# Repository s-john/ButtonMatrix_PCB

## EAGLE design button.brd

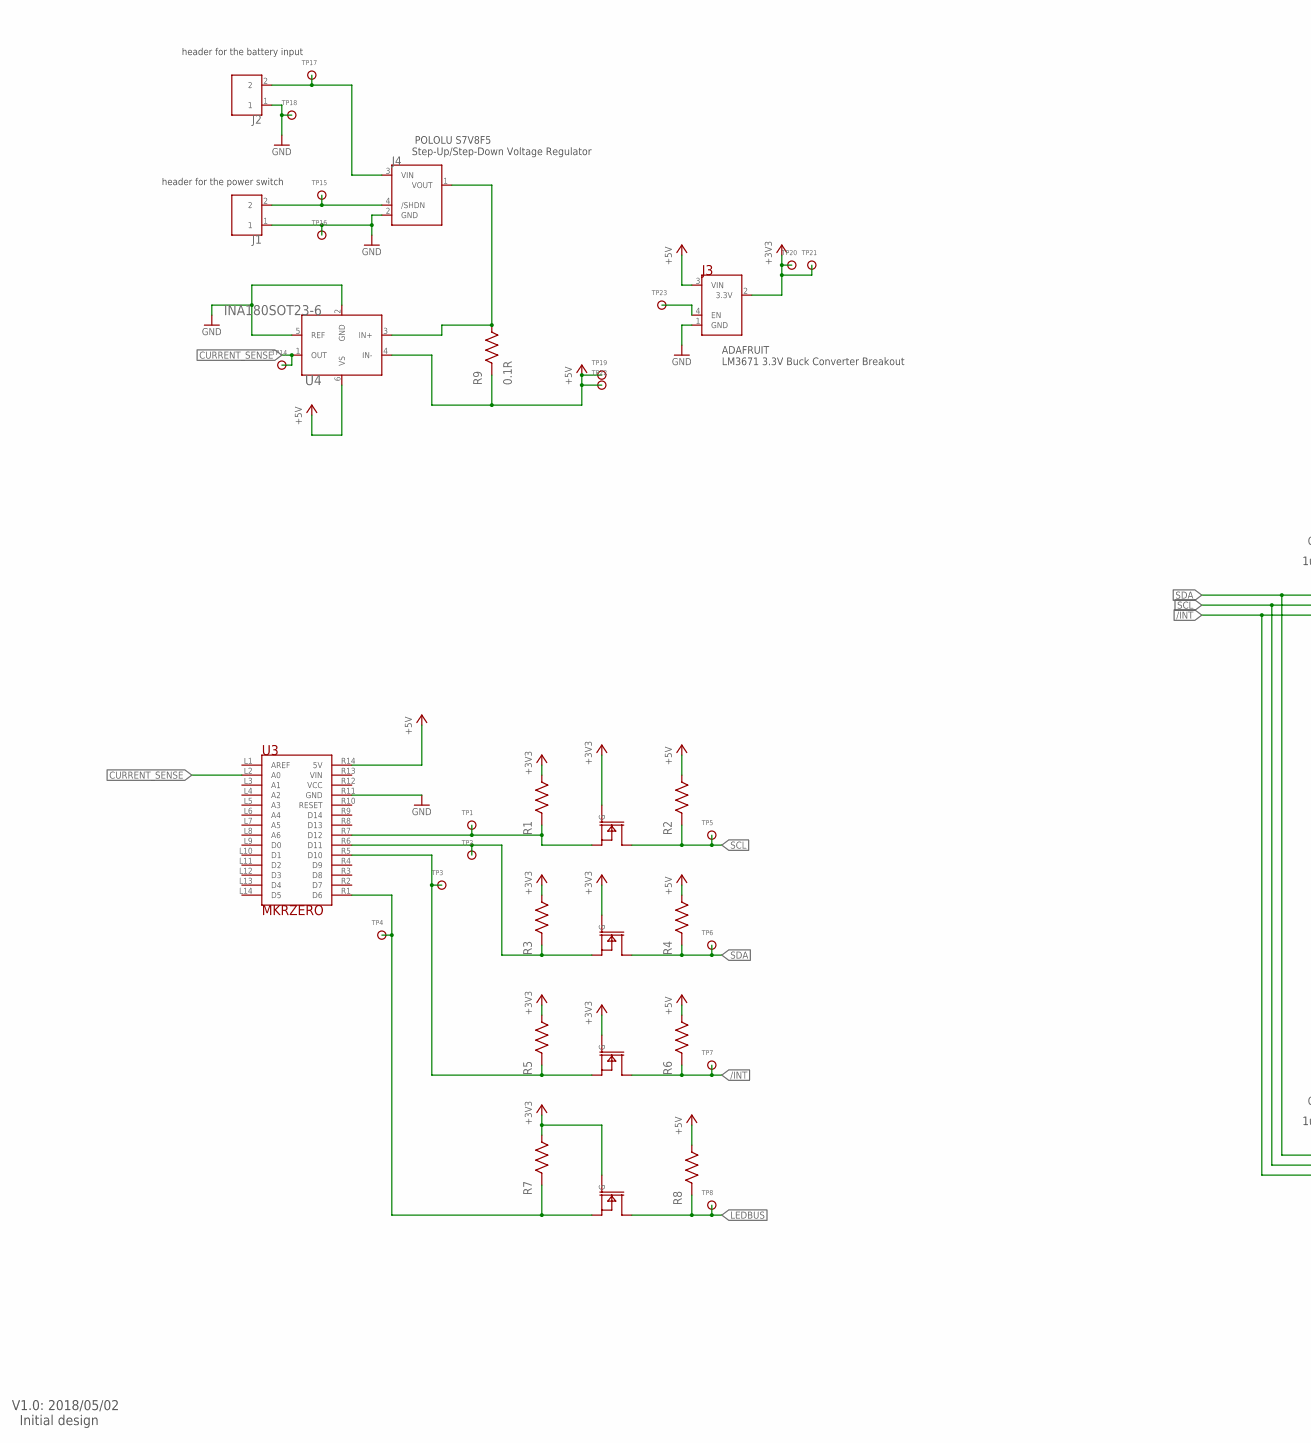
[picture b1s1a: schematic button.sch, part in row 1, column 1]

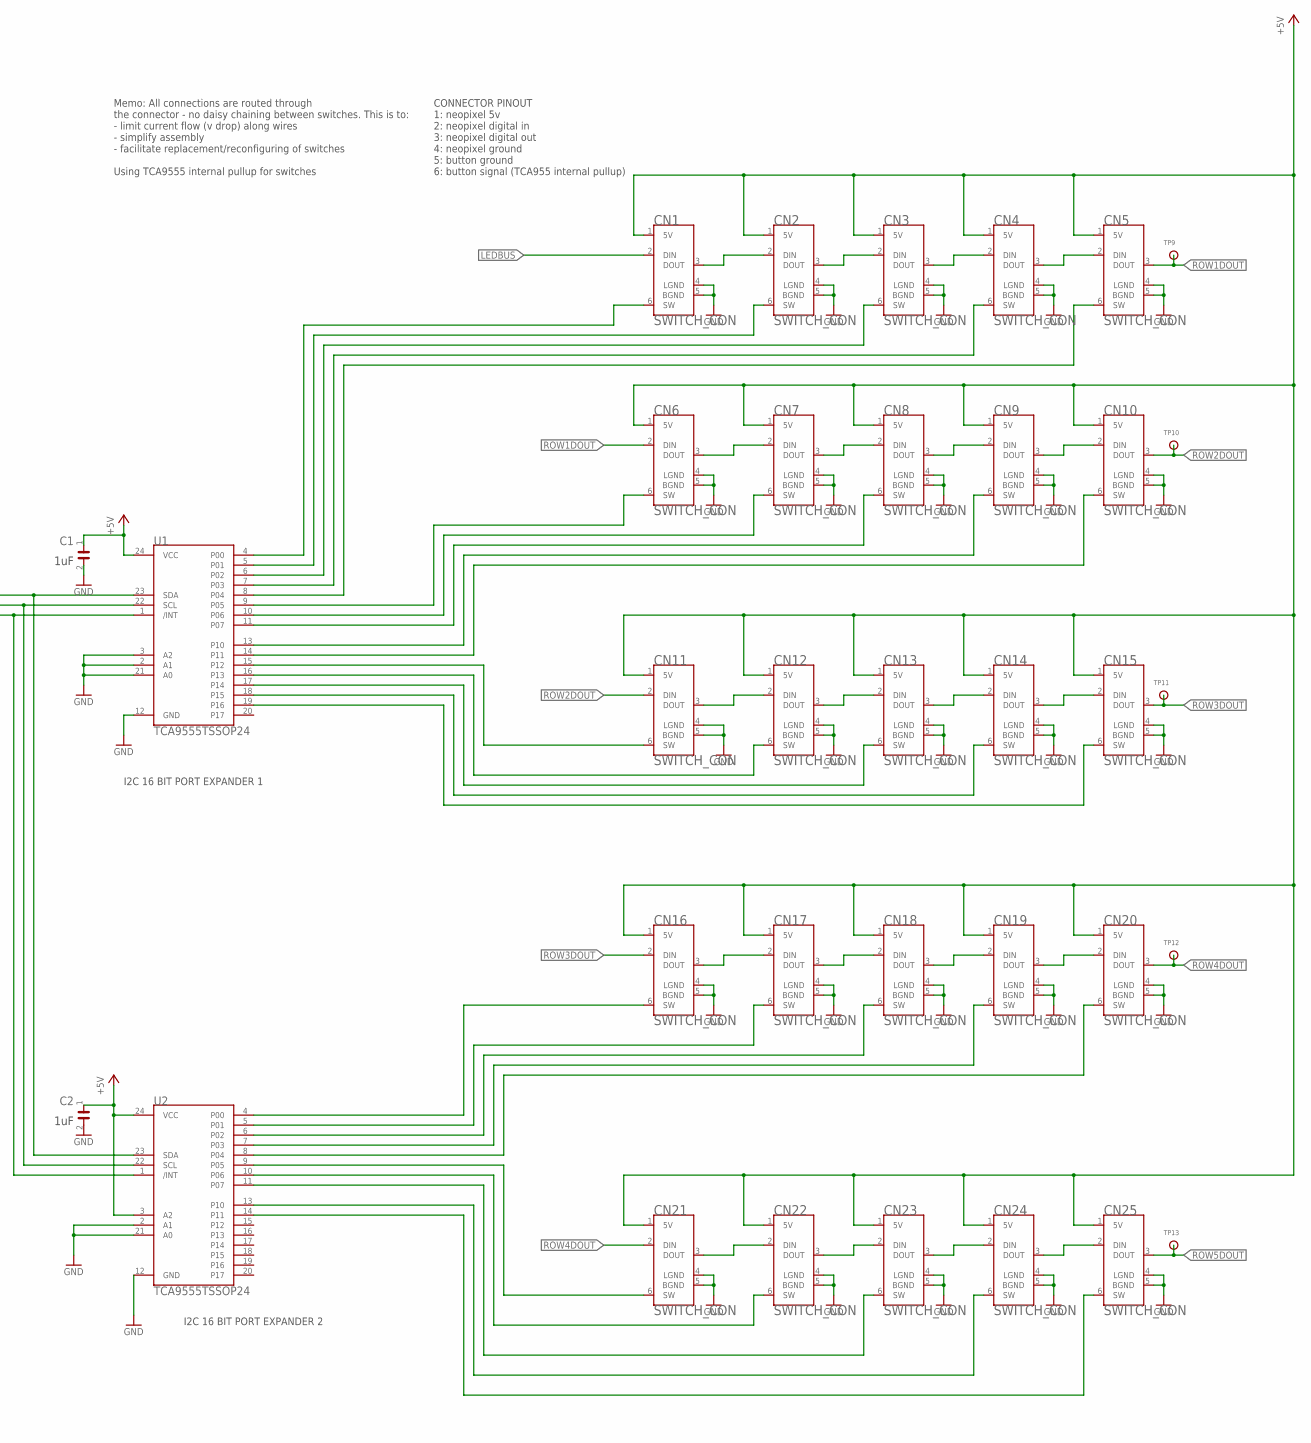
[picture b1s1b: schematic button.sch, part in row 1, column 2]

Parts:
C1, C2: 1uF; R0805
CN1, CN2, CN3, CN4, CN5, CN6, CN7, CN8, CN9, CN10, CN11, CN12, CN13, CN14, CN15, CN16, CN17, CN18, CN19, CN20, CN21, CN22, CN23, CN24, CN25: SWITCH_CON; JST_XH6
J1, J2: 2WAY_JUMPER; 2PIN_HEADER
J3: ADA-2745_3V3REG; 4PIN_HEADER
J4: S7V8F5; 4PIN_HEADER
Q1, Q2, Q3, Q4: BSS138SOT23; SOT23
R1, R2, R3, R4, R5, R6, R7, R8: RESISTOR8085; R0805
R9: 0.1R; R1206
TP1, TP2, TP3, TP4, TP5, TP6, TP7, TP8, TP9, TP10, TP11, TP12, TP13, TP14, TP15, TP16, TP17, TP18, TP19, TP20, TP21, TP22, TP23: TEST_POINT; TESTPAD_2MM
U1, U2: TCA9555TSSOP24; SOP65P640X120-24
U3: MKRZERO; ARDUINO_MKR
U4: INA180SOT23-6; SOT95P290X145-6

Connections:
+3V3: J3.2 (3.3V), Q1.1 (G), Q2.1 (G), Q3.1 (G), Q4.1 (G), R1.2, R3.2, R5.2, R7.2, TP20.P$1, TP21.P$1
+5V: C1.1, C2.1, CN1.1 (5V), CN2.1 (5V), CN3.1 (5V), CN4.1 (5V), CN5.1 (5V), CN6.1 (5V), CN7.1 (5V), CN8.1 (5V), CN9.1 (5V), CN10.1 (5V), CN11.1 (5V), CN12.1 (5V), CN13.1 (5V), CN14.1 (5V), CN15.1 (5V), CN16.1 (5V), CN17.1 (5V), CN18.1 (5V), CN19.1 (5V), CN20.1 (5V), CN21.1 (5V), CN22.1 (5V), CN23.1 (5V), CN24.1 (5V), CN25.1 (5V), J3.3 (VIN), R2.2, R4.2, R6.2, R8.2, R9.1, TP19.P$1, TP22.P$1, U1.24 (VCC), U2.3 (A2), U2.24 (VCC), U3.R14 (5V), U4.4 (IN-), U4.6 (VS)
/INT: Q2.3 (D), R6.1, TP7.P$1, U1.1 (/INT), U2.1 (/INT)
CURRENT_SENSE: TP14.P$1, U3.L2 (A0), U4.1 (OUT)
GND: C1.2, C2.2, CN1.4 (LGND), CN1.5 (BGND), CN2.4 (LGND), CN2.5 (BGND), CN3.4 (LGND), CN3.5 (BGND), CN4.4 (LGND), CN4.5 (BGND), CN5.4 (LGND), CN5.5 (BGND), CN6.4 (LGND), CN6.5 (BGND), CN7.4 (LGND), CN7.5 (BGND), CN8.4 (LGND), CN8.5 (BGND), CN9.4 (LGND), CN9.5 (BGND), CN10.4 (LGND), CN10.5 (BGND), CN11.4 (LGND), CN11.5 (BGND), CN12.4 (LGND), CN12.5 (BGND), CN13.4 (LGND), CN13.5 (BGND), CN14.4 (LGND), CN14.5 (BGND), CN15.4 (LGND), CN15.5 (BGND), CN16.4 (LGND), CN16.5 (BGND), CN17.4 (LGND), CN17.5 (BGND), CN18.4 (LGND), CN18.5 (BGND), CN19.4 (LGND), CN19.5 (BGND), CN20.4 (LGND), CN20.5 (BGND), CN21.4 (LGND), CN21.5 (BGND), CN22.4 (LGND), CN22.5 (BGND), CN23.4 (LGND), CN23.5 (BGND), CN24.4 (LGND), CN24.5 (BGND), CN25.4 (LGND), CN25.5 (BGND), J1.1, J2.1, J3.1 (GND), J4.2 (GND), TP16.P$1, TP18.P$1, U1.2 (A1), U1.3 (A2), U1.12 (GND), U1.21 (A0), U2.2 (A1), U2.12 (GND), U2.21 (A0), U3.R11 (GND), U4.2 (GND), U4.5 (REF)
LEDBUS: CN1.2 (DIN), Q4.3 (D), R8.1, TP8.P$1
unnamed: CN23.3 (DOUT), CN24.2 (DIN)
unnamed: CN24.3 (DOUT), CN25.2 (DIN)
unnamed: CN1.6 (SW), U1.4 (P00)
unnamed: CN2.6 (SW), U1.5 (P01)
unnamed: CN3.6 (SW), U1.6 (P02)
unnamed: J3.4 (EN), TP23.P$1
unnamed: CN1.3 (DOUT), CN2.2 (DIN)
unnamed: CN2.3 (DOUT), CN3.2 (DIN)
unnamed: CN3.3 (DOUT), CN4.2 (DIN)
unnamed: CN4.3 (DOUT), CN5.2 (DIN)
unnamed: CN6.3 (DOUT), CN7.2 (DIN)
unnamed: CN7.3 (DOUT), CN8.2 (DIN)
unnamed: CN8.3 (DOUT), CN9.2 (DIN)
unnamed: CN9.3 (DOUT), CN10.2 (DIN)
unnamed: CN11.3 (DOUT), CN12.2 (DIN)
unnamed: CN12.3 (DOUT), CN13.2 (DIN)
unnamed: CN13.3 (DOUT), CN14.2 (DIN)
unnamed: CN14.3 (DOUT), CN15.2 (DIN)
unnamed: CN16.3 (DOUT), CN17.2 (DIN)
unnamed: CN17.3 (DOUT), CN18.2 (DIN)
unnamed: CN18.3 (DOUT), CN19.2 (DIN)
unnamed: CN19.3 (DOUT), CN20.2 (DIN)
unnamed: CN21.3 (DOUT), CN22.2 (DIN)
unnamed: CN22.3 (DOUT), CN23.2 (DIN)
unnamed: CN4.6 (SW), U1.7 (P03)
unnamed: CN5.6 (SW), U1.8 (P04)
unnamed: CN6.6 (SW), U1.9 (P05)
unnamed: CN7.6 (SW), U1.10 (P06)
unnamed: CN8.6 (SW), U1.11 (P07)
unnamed: CN9.6 (SW), U1.13 (P10)
unnamed: CN10.6 (SW), U1.14 (P11)
unnamed: CN11.6 (SW), U1.15 (P12)
unnamed: CN12.6 (SW), U1.16 (P13)
unnamed: CN13.6 (SW), U1.17 (P14)
unnamed: CN14.6 (SW), U1.18 (P15)
unnamed: CN15.6 (SW), U1.19 (P16)
unnamed: CN16.6 (SW), U2.4 (P00)
unnamed: CN17.6 (SW), U2.5 (P01)
unnamed: CN18.6 (SW), U2.6 (P02)
unnamed: CN19.6 (SW), U2.7 (P03)
unnamed: CN20.6 (SW), U2.8 (P04)
unnamed: Q3.2 (S), R1.1, TP1.P$1, U3.R7 (D12)
unnamed: CN21.6 (SW), U2.9 (P05)
unnamed: CN22.6 (SW), U2.10 (P06)
unnamed: CN23.6 (SW), U2.11 (P07)
unnamed: CN24.6 (SW), U2.13 (P10)
unnamed: CN25.6 (SW), U2.14 (P11)
unnamed: Q4.2 (S), R7.1, TP4.P$1, U3.R1 (D6)
unnamed: Q1.2 (S), R3.1, TP2.P$1, U3.R6 (D11)
unnamed: J1.2, J4.4 (/SHDN), TP15.P$1
unnamed: J2.2, J4.3 (VIN), TP17.P$1
unnamed: Q2.2 (S), R5.1, TP3.P$1, U3.R5 (D10)
unnamed: J4.1 (VOUT), R9.2, U4.3 (IN+)
ROW1DOUT: CN5.3 (DOUT), CN6.2 (DIN), TP9.P$1
ROW2DOUT: CN10.3 (DOUT), CN11.2 (DIN), TP10.P$1
ROW3DOUT: CN15.3 (DOUT), CN16.2 (DIN), TP11.P$1
ROW4DOUT: CN20.3 (DOUT), CN21.2 (DIN), TP12.P$1
ROW5DOUT: CN25.3 (DOUT), TP13.P$1
SCL: Q3.3 (D), R2.1, TP5.P$1, U1.22 (SCL), U2.22 (SCL)
SDA: Q1.3 (D), R4.1, TP6.P$1, U1.23 (SDA), U2.23 (SDA)

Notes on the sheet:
header for the power switch
header for the battery input
POLOLU S7V8F5 Step-Up/Step-Down Voltage Regulator
ADAFRUIT LM3671 3.3V Buck Converter Breakout
CONNECTOR PINOUT 1: neopixel 5v 2: neopixel digital in 3: neopixel digital out 4: neopixel ground 5: button ground 6: button signal (TCA955 internal pullup)
I2C 16 BIT PORT EXPANDER 1
I2C 16 BIT PORT EXPANDER 2
Memo: All connections are routed through the connector - no daisy chaining between switches. This is to: - limit current flow (v drop) along wires - simplify assembly - facilitate replacement/reconfiguring of switches Using TCA9555 internal pullup for switches
V1.0: 2018/05/02 Initial design

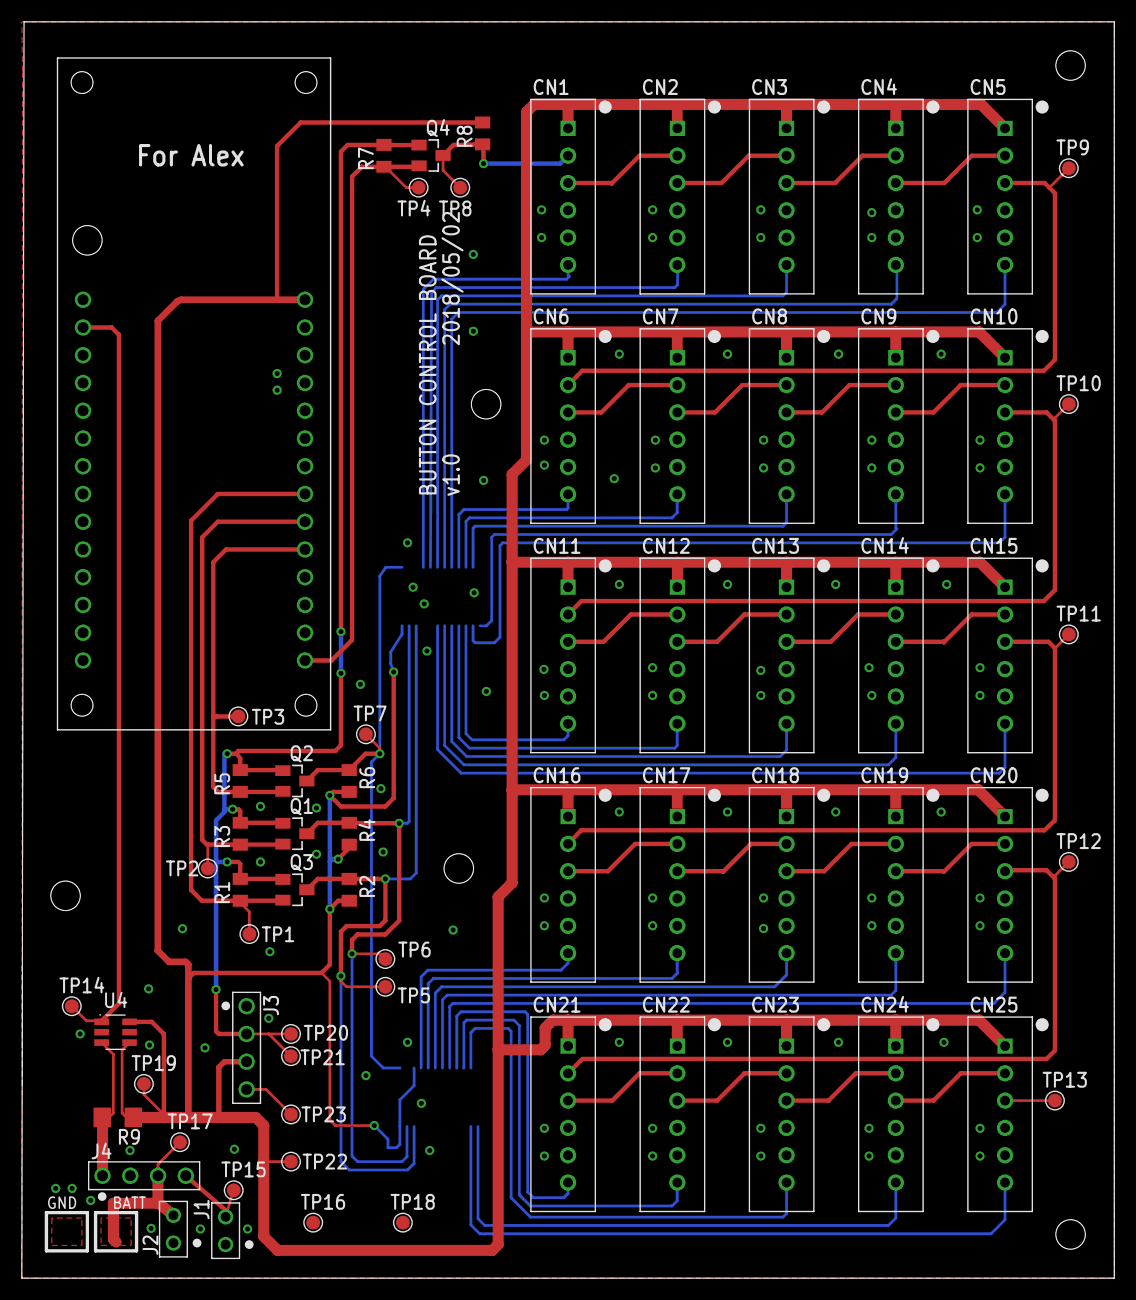
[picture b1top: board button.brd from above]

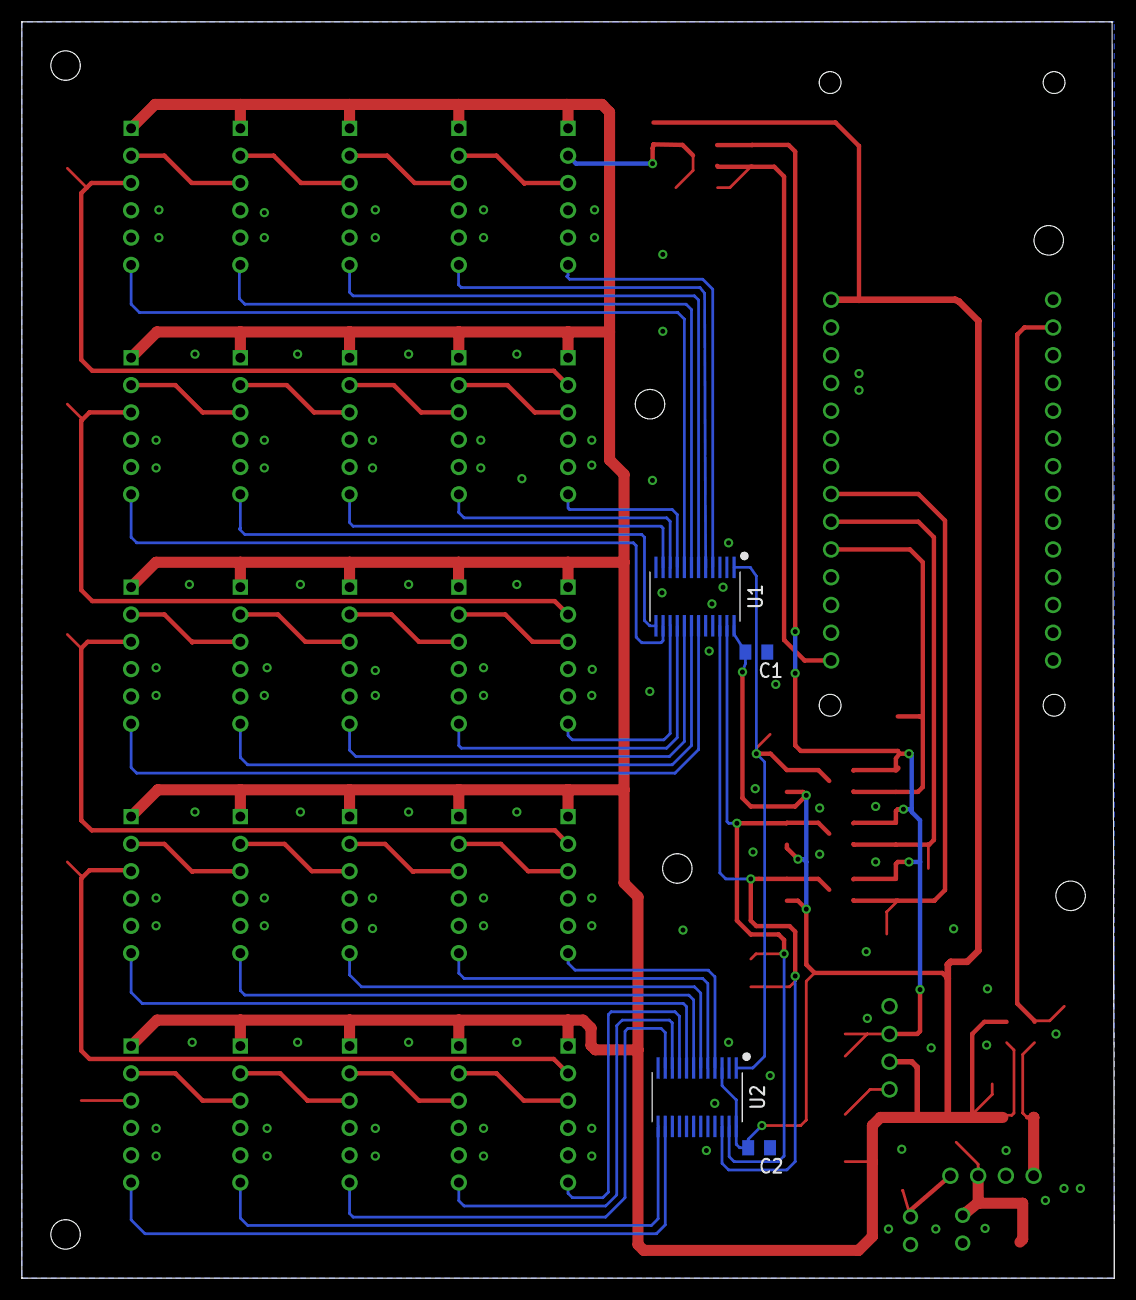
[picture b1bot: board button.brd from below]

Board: 2 copper layers, 100.0 x 115.0 mm, 71 parts (4 on the bottom side), 66 nets.

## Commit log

2018-05-03 Version 1
    Initial commit of version 1
